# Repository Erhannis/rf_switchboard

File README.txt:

KiCAD pcb; whole bunch of RF-related modules, so I can figure out what works and how.  I'm a novice, don't trust my boards too hard.

Contains:
1x RP2040 with breakout headers
1x Micro-USB connector for 5V, 3V, and programming the RP2040
2x Tayloe Detectors (1x variable gain)
3x Ferrite feedthroughs (various ends)
2x 50Ω Loads
4x Shorts
Several inductors, assorted
Several capacitors, assorted
2x Headphone jacks
2x Amplifiers (1x variable gain)
1x 50MHz high pass filter
1x 800KHz high pass filter
1x 1MHz low pass filter
2x (1-10)MHz band pass filter (two arrangements)
5x LEDs, different colors
2x Laser diodes, different colors
2x Photodiode modules (2x with variable gain, 1x with 16Hz high pass)
2x Microphones
1x Speaker
3x RF mixers (various configurations)
2x De/mux (various configurations)
1x 2.5KHz-200MHz clock
1x DC boost converter (variable)
1x Constant current source (variable)
6x Attenuators (various strengths and topologies, 2x variable)
4x Buttons
8x Junctions
2x Header pin / U.FL adapter sets (4 each)
4x RF switches (two configurations)
2x NFET/PFET pairs
...and anything else I missed.

Everything MIT licensed, except a lot of the Tayloe module stuff I got from https://github.com/michalin/easysdr licensed GPL, though most of THAT came from the original Tayloe Detector paper https://www.norcalqrp.org/files/Tayloe_mixer_x3a.pdf, so I dunno how that works exactly.

-Erhannis

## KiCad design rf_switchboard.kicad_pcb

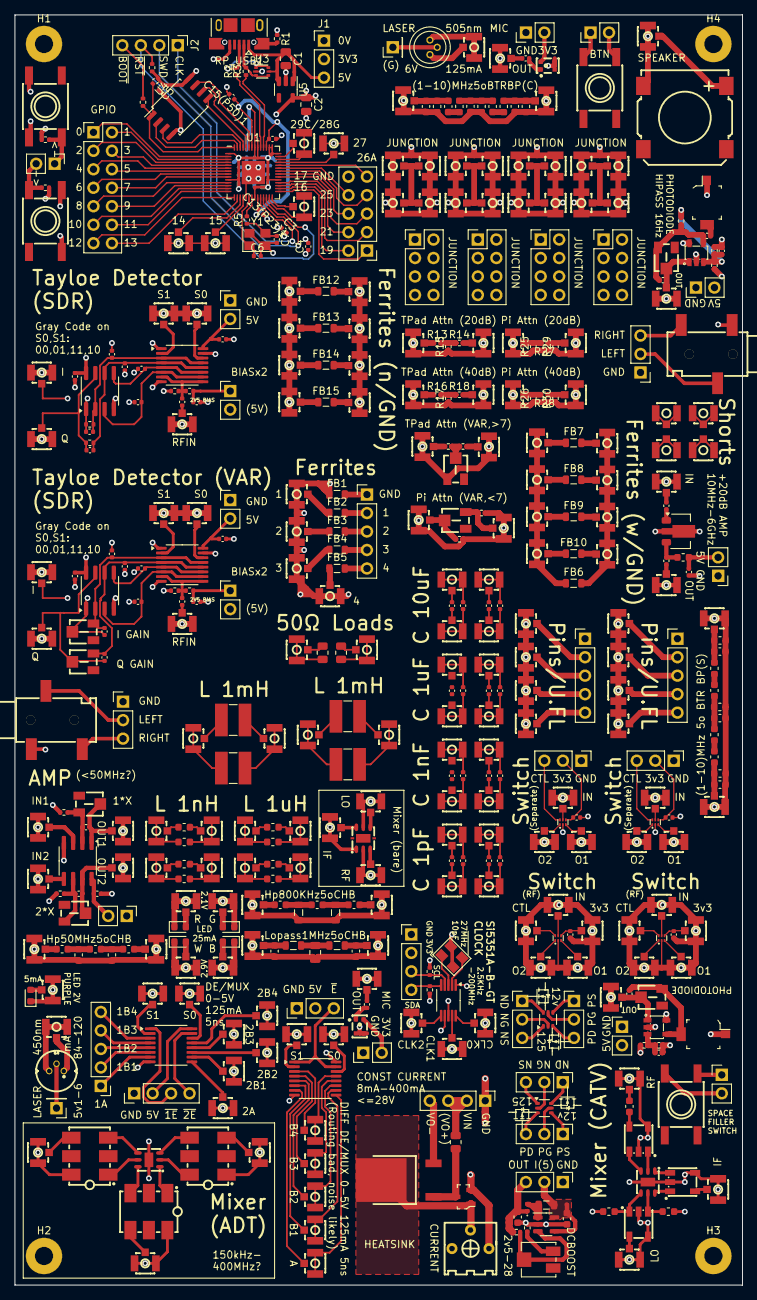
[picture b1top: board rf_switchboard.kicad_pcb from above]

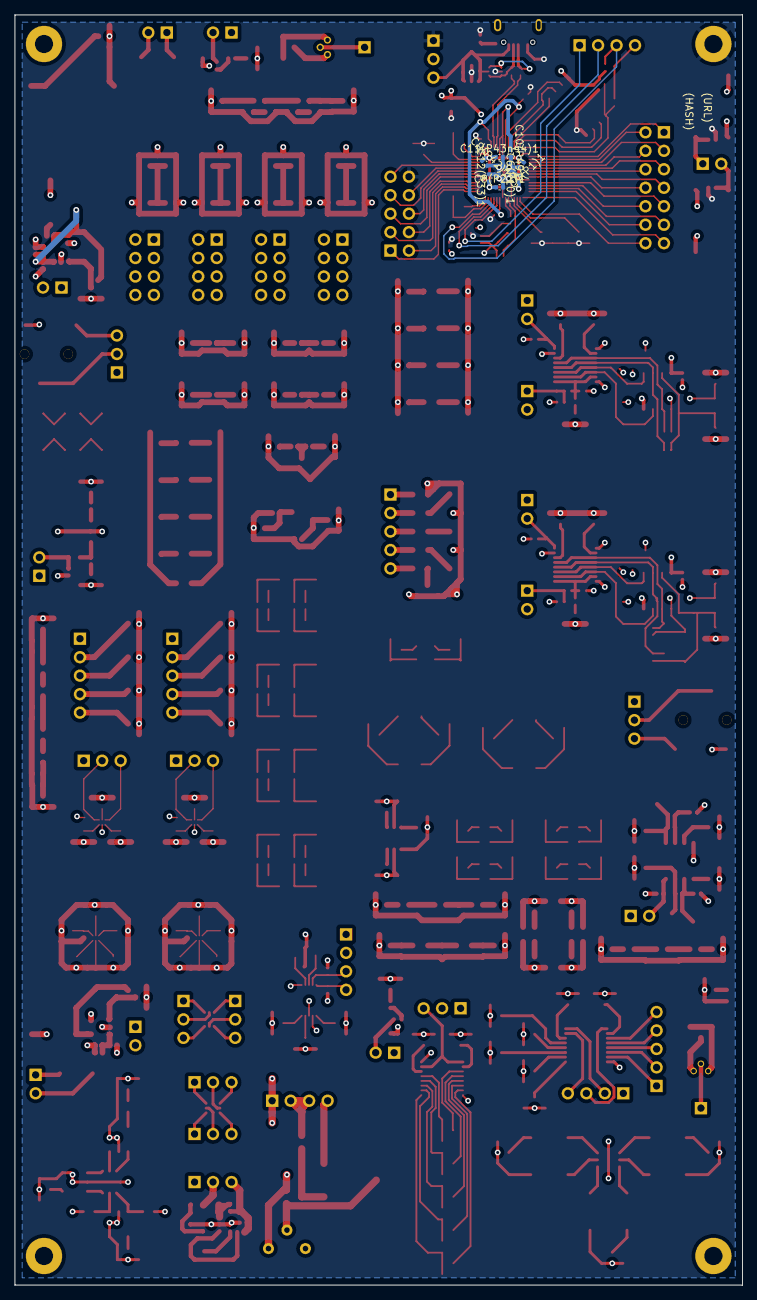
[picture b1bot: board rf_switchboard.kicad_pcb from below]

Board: 4 copper layers, 100.0 x 174.6 mm, 467 parts (7 on the bottom side), 421 nets.

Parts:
C1, C2: 10uF; C_0805_2012Metric
C1_1_10_5B1, C1_1_10_5B2, C5_1_10_5B1, C5_1_10_5B2: 218.6pF; C_0603_1608Metric
C1_HA1, C2_HA1, C3_HA1: C; C_0402_1005Metric
C1_HP1: 56pF; C_0603_1608Metric
C1_HP2, C1_LP1, C3_HP2, C3_LP1: 3.6nF; C_0603_1608Metric
C1_LA1, C2_LA1: 27pF; C_0402_1005Metric
C1_MIC1, C1_MIC2, C19, C20, C27, C28: 10uF; C_0402_1005Metric
C1_PR1, C1_PRH1: 3.3pF; C_0402_1005Metric
C1_TD1, C1_TDV1, C2_TD1, C2_TDV1, C3_TD1, C3_TDV1, C4_TD1, C4_TDV1: 220nF; C_0402_1005Metric
C1_VARB1, C2_VARB1: 10uF; C_0603_1608Metric
C2_1_10_5B1, C2_1_10_5B2, C4_1_10_5B1, C4_1_10_5B2: 1.771nF; C_0603_1608Metric
C2_HP1: 33pF; C_0603_1608Metric
C2_HP2: 2nF; C_0603_1608Metric
C2_LP1: 6.2nF; C_0805_2012Metric
C2_PR1, C2_PRH1, C3_LA1, C7_TD1, C7_TDV1, C8_TD1, C8_TDV1, C9_TD1, C9_TDV1, C11(P43n44)1, C12_TD1, C12_TDV1, C14(P45)1, C17, C18, C25, C26: 1uF; C_0402_1005Metric
C3, C4, C5, C6(P10)1, C7(P1)1, C8, C8(P22)1, C9, C9(P42)1, C10, C10(P49)1, C11, C12(P33)1, C13(P23)1, C15(P50)1: 100nF; C_0402_1005Metric
C3_1_10_5B1, C3_1_10_5B2: 707.4pF; C_0603_1608Metric
C3_HP1: 56nF; C_0603_1608Metric
C3_PRH1, C15, C16, C23, C24: 1nF; C_0402_1005Metric
C6, C7: 35pF; C_0402_1005Metric
C10_TD1, C10_TDV1, C11_TD1, C11_TDV1: 470pF; C_0402_1005Metric
C12: 3pF; C_0603_1608Metric
C13, C14, C21, C22: 1pF; C_0402_1005Metric
D1_LAS1: GH05035A2G; OPTO-TH_GH05035A2G
D1_LAS2: GH04580A2GX; LED-TH_3P-BD5.6-P1.00
D1_LEDS1: Red; LED_0603_1608Metric
D1_LEDS2: Purple; LED_0603_1608Metric
D1_VARB1: D_Schottky; D_0402_1005Metric
D2_LEDS1: Green; LED_0603_1608Metric
D3_LEDS1: Blue; LED_0603_1608Metric
D4_LEDS1: White; LED_0603_1608Metric
FB1, FB2, FB3, FB4, FB5, FB6, FB7, FB8, FB9, FB10, FB12, FB13, FB14, FB15: FerriteBead; L_0805_2012Metric
H1, H2, H3, H4: MountingHole_Pad; MountingHole_2.5mm_Pad
J1, J1_3S1, J1_3S2, J1_3S3, J1_3S4, J1_DM2, J1_VARB1: Conn_01x03_Pin; PinHeader_1x03_P2.54mm_Vertical
J1_CCV1, J1_DM1, J2, J18: Conn_01x04_Pin; PinHeader_1x04_P2.54mm_Vertical
J1_HP1, J1_HP2, J1_LAS1, J1_LAS2, J1_LEDS1, J1_LEDS2, J1_LP1, J2_DM1, J2_DM2, J2_HP1, J2_HP2, J2_LEDS1, J2_LP1, J2_MIC1, J2_MIC2, J3_DM1, J3_DM2, J3_LEDS1, J4_LEDS1, J5_DM1, J5_DM2, J6_DM1, J6_DM2, J7_DM1, J7_DM2, J8_DM1, J8_DM2, J9_DM1, J9_DM2: BWU.FL-IPEX1; IPEX-SMD_BWIPX-1-001E
J1_LA1, J1_MIC1, J1_MIC2, J1_PR1, J1_PRH1, J1_SS1, J1_SS2, J1_SS3, J10, J11, J15, J16, J19: Conn_01x02_Pin; PinHeader_1x02_P2.54mm_Vertical
J2_LAS1, J2_LAS2: Conn_01x01_Pin; PinHeader_1x01_P2.54mm_Vertical
J3, J4, J4_DM1, J5: Conn_01x05_Pin; PinHeader_1x05_P2.54mm_Vertical
J6, J7, J8, J9: Conn_02x04_Counter_Clockwise; PinHeader_2x04_P2.54mm_Vertical
J12, J13: PJ-320B; AUDIO-SMD_PJ-320B
J14: Conn_02x07_Odd_Even; PinHeader_2x07_P2.54mm_Vertical
J17: Conn_02x05_Odd_Even; PinHeader_2x05_P2.54mm_Vertical
JI1_LA1, JI2_LA1: BWU.FL-IPEX1; IPEX-SMD_BWIPX-1-001E
JN1_FET1, JN1_FET2: Conn_01x03_Pin; PinHeader_1x03_P2.54mm_Vertical
JO1_LA1, JO1_PR1, JO1_PRH1, JO2_LA1: BWU.FL-IPEX1; IPEX-SMD_BWIPX-1-001E
JP1_FET1, JP1_FET2: Conn_01x03_Pin; PinHeader_1x03_P2.54mm_Vertical
L1, L2: 4.7nH; L_0603_1608Metric
L1_1_10_5B1, L1_1_10_5B2, L5_1_10_5B1, L5_1_10_5B2: 11.59uH; L_0603_1608Metric
L1_HA1: 33uH; L_0603_1608Metric
L1_HP1, L2_HP1: 10uH; L_0603_1608Metric
L1_HP2, L2_HP2: 7.5uH; L_0805_2012Metric
L1_LP1, L2_LP1: 10uH; L_0805_2012Metric
L1_VARB1: L 10uH; L_0805_2012Metric
L2_1_10_5B1, L2_1_10_5B2, L4_1_10_5B1, L4_1_10_5B2: 1.431uH; L_0603_1608Metric
L3, L4, L5, L6: 1nH; L_0603_1608Metric
L3_1_10_5B1, L3_1_10_5B2: 3.581uH; L_0603_1608Metric
L7, L8, L11, L12: 1uH; L_0603_1608Metric
L9, L10, L13, L14: 1mH; L_Ferrocore_DLG-0403
POW1_VARB1: LM27313XMF; SOT-23-5
PV1_PR1, PV1_PRH1: BPW_34_S-Z; LED_2-SMD_Gull_Wing_4.4x3.85mm
Q1_CCV1: MOT13003D; TO-252-3_L6.5-W5.9-P4.60-LS10.0-BL
Q1_FET1, Q1_FET2: BSD235C; SOT-363_SC-70-6
Q2_CCV1: SS8050; SOT-23-3
R1: 1M; R_0402_1005Metric
R1_CCV1: 3.3k; R_0805_2012Metric
R1_LA1, R2_LA1, R6: 1k; R_0402_1005Metric
R1_PR1, R1_PRH1: 13.7k; R_0402_1005Metric
R1_SI5351AB1, R2_SI5351AB1, R4, R7: 10K; R_0402_1005Metric
R1_SS1, R2_SS1: 3.3k; R_0402_1005Metric
R1_TD1, R1_TDV1, R2_TD1, R2_TDV1, R3_TD1, R4_TD1: 10k; R_0402_1005Metric
R1_VARB1: R 100k 1%; R_0402_1005Metric
R2, R3: 27; R_0402_1005Metric
R2_PR1, R2_PRH1: 280; R_0402_1005Metric
R2_VARB1: R 4.53k 1%; R_0402_1005Metric
R3_PRH1: 10M; R_0402_1005Metric
R3_TDV1, R4_TDV1: 500k; RES-ADJ-SMD_3313J-1
R5: 1K; R_0402_1005Metric
R9, R10, R11, R12: FM8625H; DFN-6_L1.1-W0.7-P0.40-BL
R13, R14: 41.2; R_0402_1005Metric
R15: 10; R_0402_1005Metric
R16, R18: 48.7; R_0402_1005Metric
R17: 1; R_0402_1005Metric
R19, R21: 43; R_0402_1005Metric
R20, R23: 50; RES-ADJ-SMD_3313J-1
R22, R24: 200; R_0402_1005Metric
R25, R29: 62; R_0402_1005Metric
R26, R30: 51; R_0402_1005Metric
R27: 249; R_0402_1005Metric
R28: 2.49k; R_0402_1005Metric
R31, R32: 51Ω; R_0805_2012Metric
RP_USB1: USB_B_Micro; USB_Micro-B_XKB_U254-051T-4BH83-F1S
RV1_VARB1: 100k R_Potentiometer; Potentiometer_Bourns_3314J_Vertical
SPK1: GSPK1304S-8R0.5W; BUZ-SMD_4P-L13.0-W13.0-P11.4-BL
SW1_SS1, SW1_SS2, SW1_SS3, SW2_SS1: K2-1157SP-I4SW-04; SW-SMD_4P-L6.2-W6.2-P4.50-LS8.6
U1: RP2040; QFN-56-1EP_7x7mm_P0.4mm_EP3.2x3.2mm
U1_DM1, U1_DM2, U1_TD1, U1_TDV1: SN74CBT3253; TSSOP-16_4.4x5mm_P0.65mm
U1_HA1: GVA-63; SOT-89-3
U1_JU1, U1_JU2, U1_JU3, U1_JU4, U2, U2_JU1, U2_JU2, U2_JU3, U2_JU4, U3_JU1, U3_JU2, U3_JU3, U3_JU4, U4_JU1, U4_JU2, U4_JU3, U4_JU4, U6, U7, U8, U9, U10, U11, U12, U13, U14, U15, U16, U17, U18, U19, U20, U21, U22, U23, U24, U25, U26, U27, U28, U29, U30, U31, U32, U33, U34, U35, U36, U37, U38, U39, U40, U41, U42, U43, U44, U45, U47, U48, U49, U50, U51, U52, U53, U54, U55, U56, U57, U58, U59, U60, U61, U62, U63, U64, U65, U66, U67, U68, U69, U70, U72, U74, U77, U78, U79, U81, U82, U83, U84, U85, U86, U87, U88, U89, U90, U91, U92, U93, U94, U95, U96, U97, U98, U99, U100, U101, U102, U103, U104, U105, U106, U107, U108, U109, U110, U111, U112, U113, U114, U115, U116, U117, U118, U119, U120, U121, U122, U123, U124, U125, U126, U127, U128, U129, U130, U131, U132, U133, U134: BWU.FL-IPEX1; IPEX-SMD_BWIPX-1-001E
U1_LA1, U2_TD1, U2_TDV1: LM4562; SOIC-8_3.9x4.9mm_P1.27mm
U1_MIC1, U1_MIC2: ZTS6117H; MIC-SMD_4P-L2.8-W1.9-P1.84-TL_ZTS6117
U1_PR1, U1_PRH1: OPA320AIDBVR; SOT-23-5_L3.0-W1.7-P0.95-LS2.8-BR
U1_SI5351AB1: Si5351A-B-GT; MSOP-10_3x3mm_P0.5mm
U3: USBLC6-2P6; SOT-666
U4: W25Q128JVS; SOIC-8_5.23x5.23mm_P1.27mm
U5: AP2112K-3.3; SOT-23-5
U46, U73, U80: PE4140B-Z; DFN-6_L3.0-W3.0-P0.95-BL-EP-PE4140B-Z
U71, U75, U76: ETC1.6-4-2-3TR; FILTER-SMD_ETC4-1-2TR
VR1_CCV1: 3362P-1-101LF; RES-ADJ-TH_3362P-1-104LF
VR1_LA1, VR2_LA1: 500k; RES-ADJ-SMD_3313J-1
VR1_PR1, VR1_PRH1: 2M; RES-ADJ-SMD_3313J-1
X1, X2, X3: ADT1-1+; XFMR-SMD_6P-L7.9-W5.6-P2.54-LS7.0-BL
X1_SI5351AB1: 27MHz; OSC-SMD_4P-L3.2-W2.5-BL
Y1: 12MHz; Crystal_SMD_3225-4Pin_3.2x2.5mm

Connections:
+1V2: C13(P23)1.1, C14(P45)1.1, C15(P50)1.1, U1.23 (DVDD), U1.45 (VREG_VOUT), U1.50 (DVDD)
+3V3: C2.1, C3.1, C4.1, C5.1, C6(P10)1.1, C7(P1)1.1, C8(P22)1.1, C9(P42)1.1, C10(P49)1.1, C11(P43n44)1.1, C12(P33)1.1, J1.2, R4.1, R7.2, SW1_SS1.3, SW1_SS1.4, SW2_SS1.3, SW2_SS1.4, U1.1 (IOVDD), U1.10 (IOVDD), U1.22 (IOVDD), U1.33 (IOVDD), U1.42 (IOVDD), U1.43 (ADC_AVDD), U1.44 (VREG_IN), U1.48 (USB_VDD), U1.49 (IOVDD), U4.8 (VCC), U5.5 (VOUT)
+5V: C1.1, J1.3, RP_USB1.1 (VBUS), U3.5 (VBUS), U5.1 (VIN), U5.3 (EN)
/1_10_5x_butter1/IN+: C1_1_10_5B2.1, C2_1_10_5B2.1, L1_1_10_5B2.1, U9.1
/1_10_5x_butter1/IN-: C1_1_10_5B2.2, C3_1_10_5B2.2, C5_1_10_5B2.2, L1_1_10_5B2.2, L3_1_10_5B2.2, L5_1_10_5B2.2, U9.2, U9.3, U10.2, U10.3
/1_10_5x_butter1/OUT+: C5_1_10_5B2.1, L4_1_10_5B2.2, L5_1_10_5B2.1, U10.1
/1_10_5x_butter/IN+: C1_1_10_5B1.1, C2_1_10_5B1.1, L1_1_10_5B1.1, U7.1
/1_10_5x_butter/IN-: C1_1_10_5B1.2, C3_1_10_5B1.2, C5_1_10_5B1.2, L1_1_10_5B1.2, L3_1_10_5B1.2, L5_1_10_5B1.2, U7.2, U7.3, U8.2, U8.3
/1_10_5x_butter/OUT+: C5_1_10_5B1.1, L4_1_10_5B1.2, L5_1_10_5B1.1, U8.1
/QSPI_CS: R6.1, R7.1, U1.56 (QSPI_SS), U4.1 (~CS)
/QSPI_DATA[0]: U1.53 (QSPI_SD0), U4.5 (DI(IO0))
/QSPI_DATA[1]: U1.55 (QSPI_SD1), U4.2 (DO(IO1))
/QSPI_DATA[2]: U1.54 (QSPI_SD2), U4.3 (IO2)
/QSPI_DATA[3]: U1.51 (QSPI_SD3), U4.7 (IO3)
/QSPI_SCK: U1.52 (QSPI_SCLK), U4.6 (CLK)
/RP_SWCLK: J2.1, U1.24 (SWCLK)
/RP_SWD: J2.2, U1.25 (SWD)
/RP_UD+: R2.1, U1.47 (USB_DP)
/RP_UD-: R3.1, U1.46 (USB_DM)
/USB_BOOT: J2.4, R6.2
/const_current_var1/GND: J1_CCV1.1, Q2_CCV1.2 (E), VR1_CCV1.3
/const_current_var1/VIN: J1_CCV1.2, J1_CCV1.3, R1_CCV1.1
/const_current_var1/VO-: J1_CCV1.4, Q1_CCV1.3 (C)
/dc_boost_var1/GND: C1_VARB1.1, C2_VARB1.1, J1_VARB1.1, POW1_VARB1.2 (GND), R2_VARB1.2
/dc_boost_var1/VIN: C1_VARB1.2, J1_VARB1.2, L1_VARB1.1, POW1_VARB1.4 (EN), POW1_VARB1.5 (VIN)
/dc_boost_var1/VOUT: C2_VARB1.2, D1_VARB1.1 (K), J1_VARB1.3, R1_VARB1.1
/hi_amp1/5V: C2_HA1.1, J19.2, L1_HA1.1
/hi_amp1/GND: C2_HA1.2, J19.1, U1_HA1.2 (GND), U133.2, U133.3, U134.2, U134.3
/hi_amp1/RFIN: C1_HA1.1, U133.1
/hi_amp1/RFOUT: C3_HA1.2, U134.1
/lo_amp1/5V: C3_LA1.1, J1_LA1.2, U1_LA1.8 (V+)
/lo_amp1/GND: C3_LA1.2, J1_LA1.1, JI1_LA1.2, JI1_LA1.3, JI2_LA1.2, JI2_LA1.3, JO1_LA1.2, JO1_LA1.3, JO2_LA1.2, JO2_LA1.3, R1_LA1.2, R2_LA1.2, U1_LA1.4 (V-)
/lo_amp1/IN1: JI1_LA1.1, U1_LA1.3 (+)
/lo_amp1/IN2: JI2_LA1.1, U1_LA1.5 (+)
/lo_amp1/OUT1: C1_LA1.2, JO1_LA1.1, U1_LA1.1, VR1_LA1.2
/lo_amp1/OUT2: C2_LA1.2, JO2_LA1.1, U1_LA1.7, VR2_LA1.2
/mixer_catv/GND: L1.2, L2.2, U70.2, U70.3, U71.2 (S), U71.5, U72.2, U72.3, U73.7 (PAD), U74.2, U74.3, U75.2 (S), U75.4, U76.2 (S), U76.4
/photo_rx1/5V: J1_PR1.2, R1_PR1.1, U1_PR1.5 (V+)
/photo_rx1/GND: C2_PR1.2, J1_PR1.1, JO1_PR1.2, JO1_PR1.3, PV1_PR1.A, R2_PR1.2, U1_PR1.2 (V-)
/photo_rx1/OUT: C1_PR1.2, JO1_PR1.1, U1_PR1.1 (OUT), VR1_PR1.2
/photo_rx_highpass1/5V: J1_PRH1.2, R1_PRH1.1, U1_PRH1.5 (V+)
/photo_rx_highpass1/GND: C2_PRH1.2, J1_PRH1.1, JO1_PRH1.2, JO1_PRH1.3, PV1_PRH1.A, R2_PRH1.2, U1_PRH1.2 (V-)
/photo_rx_highpass1/OUT: C1_PRH1.2, JO1_PRH1.1, U1_PRH1.1 (OUT), VR1_PRH1.2
/si5351ab1/3V3: J18.2, R1_SI5351AB1.1, R2_SI5351AB1.1, U1_SI5351AB1.1 (VDD), U1_SI5351AB1.7 (VDDO)
/si5351ab1/CLK0: U1_SI5351AB1.10 (CLK0), U130.1
/si5351ab1/CLK1: U1_SI5351AB1.9 (CLK1), U131.1
/si5351ab1/CLK2: U1_SI5351AB1.6 (CLK2), U132.1
/si5351ab1/GND: J18.1, U1_SI5351AB1.8 (GND), U130.2, U130.3, U131.2, U131.3, U132.2, U132.3, X1_SI5351AB1.2 (GND), X1_SI5351AB1.4 (GND)
/si5351ab1/SCL: J18.3, R1_SI5351AB1.2, U1_SI5351AB1.4 (SCL)
/si5351ab1/SDA: J18.4, R2_SI5351AB1.2, U1_SI5351AB1.5 (SDA)
/tayloe_detector/5V: C8_TD1.2, C12_TD1.1, J10.2, J15.2, U1_TD1.16 (VCC), U2_TD1.8 (V+)
/tayloe_detector/BIASx2: C9_TD1.1, J15.1, R1_TD1.1
/tayloe_detector/GND: C1_TD1.2, C2_TD1.2, C3_TD1.2, C4_TD1.2, C8_TD1.1, C9_TD1.2, C12_TD1.2, J10.1, R2_TD1.2, U1_TD1.1 (1~OE), U1_TD1.8 (GND), U1_TD1.15 (2~OE), U2_TD1.4 (V-), U78.2, U78.3, U79.2, U79.3, U82.2, U82.3, U84.2, U84.3, U85.2, U85.3
/tayloe_detector/I: C10_TD1.2, R3_TD1.2, U2_TD1.1, U84.1
/tayloe_detector/Q: C11_TD1.2, R4_TD1.2, U2_TD1.7, U85.1
/tayloe_detector/RFIN: C7_TD1.1, U78.1
/tayloe_detector/S0: U1_TD1.14 (S0), U79.1
/tayloe_detector/S1: U1_TD1.2 (S1), U82.1
/tayloe_detector_var/5V: C8_TDV1.2, C12_TDV1.1, J11.2, J16.2, U1_TDV1.16 (VCC), U2_TDV1.8 (V+)
/tayloe_detector_var/BIASx2: C9_TDV1.1, J16.1, R1_TDV1.1
/tayloe_detector_var/GND: C1_TDV1.2, C2_TDV1.2, C3_TDV1.2, C4_TDV1.2, C8_TDV1.1, C9_TDV1.2, C12_TDV1.2, J11.1, R2_TDV1.2, U1_TDV1.1 (1~OE), U1_TDV1.8 (GND), U1_TDV1.15 (2~OE), U2_TDV1.4 (V-), U86.2, U86.3, U87.2, U87.3, U88.2, U88.3, U89.2, U89.3, U90.2, U90.3
/tayloe_detector_var/I: C10_TDV1.2, R3_TDV1.2, U2_TDV1.1, U89.1
/tayloe_detector_var/Q: C11_TDV1.2, R4_TDV1.2, U2_TDV1.7, U90.1
/tayloe_detector_var/RFIN: C7_TDV1.1, U88.1
/tayloe_detector_var/S0: U1_TDV1.14 (S0), U86.1
/tayloe_detector_var/S1: U1_TDV1.2 (S1), U87.1
/~RESET: J2.3, R4.2, U1.26 (RUN)
GND: C1.2, C2.2, C3.2, C4.2, C5.2, C6.2, C6(P10)1.2, C7.2, C7(P1)1.2, C8(P22)1.2, C9(P42)1.2, C10(P49)1.2, C11(P43n44)1.2, C12(P33)1.2, C13(P23)1.2, C14(P45)1.2, C15(P50)1.2, H1.1, J1.1, J17.10, R1.1, R1_SS1.1, R2_SS1.2, RP_USB1.5 (GND), U1.19 (TESTEN), U1.57 (GND), U3.2 (GND), U4.4 (GND), U5.2 (GND), U126.2, U126.3, U128.2, U128.3, U129.2, U129.3, Y1.2, Y1.4
GND_DM1: J1_DM1.1, J2_DM1.2, J2_DM1.3, J3_DM1.2, J3_DM1.3, J5_DM1.2, J5_DM1.3, J6_DM1.2, J6_DM1.3, J7_DM1.2, J7_DM1.3, J8_DM1.2, J8_DM1.3, J9_DM1.2, J9_DM1.3, U1_DM1.8 (GND)
GND_DM2: J1_DM2.1, J2_DM2.2, J2_DM2.3, J3_DM2.2, J3_DM2.3, U1_DM2.8 (GND)
unnamed: C1_HA1.2, U1_HA1.1
unnamed: C1_HP1.1, J1_HP1.1
unnamed: C1_HP1.2, C2_HP1.1, L1_HP1.2
unnamed: C1_HP2.1, J1_HP2.1
unnamed: C1_HP2.2, C2_HP2.1, L1_HP2.2
unnamed: C1_LP1.1, J1_LP1.1, L1_LP1.1
unnamed: C1_LP1.2, C2_LP1.2, C3_LP1.2, J1_LP1.2, J1_LP1.3, J2_LP1.2, J2_LP1.3
unnamed: C1_MIC1.1, J2_MIC1.1
unnamed: C1_MIC2.1, J2_MIC2.1
unnamed: C2_1_10_5B1.2, L2_1_10_5B1.1
unnamed: C2_1_10_5B2.2, L2_1_10_5B2.1
unnamed: C2_HP1.2, C3_HP1.1, L2_HP1.2
unnamed: C2_HP2.2, C3_HP2.1, L2_HP2.2
unnamed: C2_LP1.1, L1_LP1.2, L2_LP1.1
unnamed: C3_1_10_5B1.1, C4_1_10_5B1.1, L2_1_10_5B1.2, L3_1_10_5B1.1
unnamed: C3_1_10_5B2.1, C4_1_10_5B2.1, L2_1_10_5B2.2, L3_1_10_5B2.1
unnamed: C3_HA1.1, L1_HA1.2, U1_HA1.3
unnamed: C3_HP1.2, J2_HP1.1
unnamed: C3_HP2.2, J2_HP2.1
unnamed: C3_LP1.1, J2_LP1.1, L2_LP1.2
unnamed: C3_PRH1.1, PV1_PRH1.K
unnamed: C4_1_10_5B1.2, L4_1_10_5B1.1
unnamed: C4_1_10_5B2.2, L4_1_10_5B2.1
unnamed: C7.1, R5.1, Y1.3
unnamed: C12.1, U70.1
unnamed: C12.2, U71.4
unnamed: C13.1, U103.1
unnamed: C13.2, U104.1
unnamed: C14.1, U103.2, U103.3
unnamed: C14.2, U104.2, U104.3
unnamed: C15.1, U105.1
unnamed: C15.2, U106.1
unnamed: C16.1, U105.2, U105.3
unnamed: C16.2, U106.2, U106.3
unnamed: C17.1, U107.1
unnamed: C17.2, U108.1
unnamed: C18.1, U107.2, U107.3
unnamed: C18.2, U108.2, U108.3
unnamed: C19.1, U109.1
unnamed: C19.2, U110.1
unnamed: C20.1, U109.2, U109.3
unnamed: C20.2, U110.2, U110.3
unnamed: C21.1, U111.1
unnamed: C21.2, U115.1
unnamed: C22.1, U111.2, U111.3
unnamed: C22.2, U115.2, U115.3
unnamed: C23.1, U112.1
unnamed: C23.2, U116.1
unnamed: C24.1, U112.2, U112.3
unnamed: C24.2, U116.2, U116.3
unnamed: C25.1, U113.1
unnamed: C25.2, U117.1
unnamed: C26.1, U113.2, U113.3
unnamed: C26.2, U117.2, U117.3
unnamed: C27.1, U114.1
unnamed: C27.2, U118.1
unnamed: C28.1, U114.2, U114.3
unnamed: C28.2, U118.2, U118.3
unnamed: D1_LAS1.1 (A), J1_LAS1.1
unnamed: D1_LAS1.3 (K), J1_LAS1.2, J1_LAS1.3
unnamed: D1_LAS2.1 (A), J1_LAS2.1
unnamed: D1_LAS2.3 (K), J1_LAS2.2, J1_LAS2.3
unnamed: D1_LEDS1.2 (A), J1_LEDS1.1
unnamed: D1_LEDS1.1 (K), J1_LEDS1.2, J1_LEDS1.3
unnamed: D1_LEDS2.2 (A), J1_LEDS2.1
unnamed: D1_LEDS2.1 (K), J1_LEDS2.2, J1_LEDS2.3
unnamed: D1_VARB1.2 (A), L1_VARB1.2, POW1_VARB1.1 (SW)
unnamed: D2_LEDS1.2 (A), J2_LEDS1.1
unnamed: D2_LEDS1.1 (K), J2_LEDS1.2, J2_LEDS1.3
unnamed: D3_LEDS1.2 (A), J3_LEDS1.1
unnamed: D3_LEDS1.1 (K), J3_LEDS1.2, J3_LEDS1.3
unnamed: D4_LEDS1.2 (A), J4_LEDS1.1
unnamed: D4_LEDS1.1 (K), J4_LEDS1.2, J4_LEDS1.3
unnamed: FB1.1, U26.2, U26.3, U27.2, U27.3, U28.2, U28.3, U29.2, U29.3
unnamed: FB2.1, U26.1
unnamed: FB3.1, U27.1
unnamed: FB4.1, U28.1
unnamed: FB5.1, U29.1
unnamed: FB6.1, U30.2, U30.3, U31.2, U31.3, U32.2, U32.3, U33.2, U33.3
unnamed: FB6.2, U34.2, U34.3, U35.2, U35.3, U36.2, U36.3, U37.2, U37.3
unnamed: FB7.1, U30.1
unnamed: FB7.2, U34.1
unnamed: FB8.1, U31.1
unnamed: FB8.2, U35.1
unnamed: FB9.1, U32.1
unnamed: FB9.2, U36.1
unnamed: FB10.1, U33.1
unnamed: FB10.2, U37.1
unnamed: FB12.1, U59.1
unnamed: FB12.2, U60.1
unnamed: FB13.1, U61.1
unnamed: FB13.2, U62.1
unnamed: FB14.1, U63.1
unnamed: FB14.2, U64.1
unnamed: FB15.1, U65.1
unnamed: FB15.2, U66.1
unnamed: C8.1, J1_3S1.1, R9.2 (GND)
unnamed: C8.2, J1_3S1.2, R9.4 (VDD)
unnamed: J1_3S1.3, R9.6 (VCTL)
unnamed: C10.1, J1_3S2.1, R12.2 (GND)
unnamed: C10.2, J1_3S2.2, R12.4 (VDD)
unnamed: J1_3S2.3, R12.6 (VCTL)
unnamed: J1_3S3.1, J12.1
unnamed: J1_3S3.2, J12.2
unnamed: J1_3S3.3, J12.3
unnamed: J1_3S4.1, J13.1
unnamed: J1_3S4.2, J13.2
unnamed: J1_3S4.3, J13.3
unnamed: J1_DM1.2, U1_DM1.16 (VCC)
unnamed: J1_DM1.3, U1_DM1.1 (1~OE)
unnamed: J1_DM1.4, U1_DM1.15 (2~OE)
unnamed: J1_DM2.2, U1_DM2.16 (VCC)
unnamed: J1_DM2.3, U1_DM2.1 (1~OE), U1_DM2.15 (2~OE)
unnamed: J1_HP1.2, J1_HP1.3, J2_HP1.2, J2_HP1.3, L1_HP1.1, L2_HP1.1
unnamed: J1_HP2.2, J1_HP2.3, J2_HP2.2, J2_HP2.3, L1_HP2.1, L2_HP2.1
unnamed: J1_MIC1.1, J2_MIC1.2, J2_MIC1.3, U1_MIC1.2 (GND), U1_MIC1.3 (GND)
unnamed: J1_MIC1.2, U1_MIC1.4 (VDD)
unnamed: J1_MIC2.1, J2_MIC2.2, J2_MIC2.3, U1_MIC2.2 (GND), U1_MIC2.3 (GND)
unnamed: J1_MIC2.2, U1_MIC2.4 (VDD)
unnamed: J1_SS1.1, R1_SS1.2, SW1_SS1.2
unnamed: J1_SS1.2, R2_SS1.1, SW2_SS1.2
unnamed: J1_SS2.1, SW1_SS2.2
unnamed: J1_SS2.2, SW1_SS2.4
unnamed: J1_SS3.1, SW1_SS3.4
unnamed: J1_SS3.2, SW1_SS3.2
unnamed: D1_LAS1.2 (K), J2_LAS1.1
unnamed: D1_LAS2.2, J2_LAS2.1
unnamed: J3.1, U38.2, U38.3, U39.2, U39.3, U40.2, U40.3, U41.2, U41.3
unnamed: J3.2, U38.1
unnamed: J3.3, U39.1
unnamed: J3.4, U40.1
unnamed: J3.5, U41.1
unnamed: FB1.2, J4.1
unnamed: FB2.2, J4.2
unnamed: FB3.2, J4.3
unnamed: FB4.2, J4.4
unnamed: FB5.2, J4.5
unnamed: J4_DM1.1, U1_DM1.7 (1A)
unnamed: J4_DM1.2, U1_DM1.6 (1B1)
unnamed: J4_DM1.3, U1_DM1.5 (1B2)
unnamed: J4_DM1.4, U1_DM1.4 (1B3)
unnamed: J4_DM1.5, U1_DM1.3 (1B4)
unnamed: J5.1, U42.2, U42.3, U43.2, U43.3, U44.2, U44.3, U45.2, U45.3
unnamed: J5.2, U42.1
unnamed: J5.3, U43.1
unnamed: J5.4, U44.1
unnamed: J5.5, U45.1
unnamed: J6.1, J6.2, J6.3, J6.4, J6.5, J6.6, J6.7, J6.8
unnamed: J7.1, J7.2, J7.3, J7.4, J7.5, J7.6, J7.7, J7.8
unnamed: J8.1, J8.2, J8.3, J8.4, J8.5, J8.6, J8.7, J8.8
unnamed: J9.1, J9.2, J9.3, J9.4, J9.5, J9.6, J9.7, J9.8
unnamed: J14.1, U1.2 (GPIO0)
unnamed: J14.2, U1.3 (GPIO1)
unnamed: J14.3, U1.4 (GPIO2)
unnamed: J14.4, U1.5 (GPIO3)
unnamed: J14.5, U1.6 (GPIO4)
unnamed: J14.6, U1.7 (GPIO5)
unnamed: J14.7, U1.8 (GPIO6)
unnamed: J14.8, U1.9 (GPIO7)
unnamed: J14.9, U1.11 (GPIO8)
unnamed: J14.10, U1.12 (GPIO9)
unnamed: J14.11, U1.13 (GPIO10)
unnamed: J14.12, U1.14 (GPIO11)
unnamed: J14.13, U1.15 (GPIO12)
unnamed: J14.14, U1.16 (GPIO13)
unnamed: J17.1, U1.29 (GPIO18)
unnamed: J17.2, U1.30 (GPIO19)
unnamed: J17.3, U1.31 (GPIO20)
unnamed: J17.4, U1.32 (GPIO21)
unnamed: J17.5, U1.34 (GPIO22)
unnamed: J17.6, U1.35 (GPIO23)
unnamed: J17.7, U1.36 (GPIO24)
unnamed: J17.8, U1.37 (GPIO25)
unnamed: J17.9, U1.38 (GPIO26_ADC0)
unnamed: JN1_FET1.1, Q1_FET1.6 (DN)
unnamed: JN1_FET1.2, Q1_FET1.2 (GN)
unnamed: JN1_FET1.3, Q1_FET1.1 (SN)
unnamed: JN1_FET2.1, Q1_FET2.6 (DN)
unnamed: JN1_FET2.2, Q1_FET2.2 (GN)
unnamed: JN1_FET2.3, Q1_FET2.1 (SN)
unnamed: JP1_FET1.1, Q1_FET1.4 (SP)
unnamed: JP1_FET1.2, Q1_FET1.5 (GP)
unnamed: JP1_FET1.3, Q1_FET1.3 (DP)
unnamed: JP1_FET2.1, Q1_FET2.4 (SP)
unnamed: JP1_FET2.2, Q1_FET2.5 (GP)
unnamed: JP1_FET2.3, Q1_FET2.3 (DP)
unnamed: L3.1, U91.1
unnamed: L3.2, U92.1
unnamed: L4.1, U91.2, U91.3
unnamed: L4.2, U92.2, U92.3
unnamed: L5.1, U93.1
unnamed: L5.2, U94.1
unnamed: L6.1, U93.2, U93.3
unnamed: L6.2, U94.2, U94.3
unnamed: L7.1, U95.1
unnamed: L7.2, U96.1
unnamed: L8.1, U95.2, U95.3
unnamed: L8.2, U96.2, U96.3
unnamed: L9.1, U97.1
unnamed: L9.2, U98.1
unnamed: L10.1, U97.2, U97.3
unnamed: L10.2, U98.2, U98.3
unnamed: L11.1, U99.1
unnamed: L11.2, U100.1
unnamed: L12.1, U99.2, U99.3
unnamed: L12.2, U100.2, U100.3
unnamed: L13.1, U101.1
unnamed: L13.2, U102.1
unnamed: L14.1, U101.2, U101.3
unnamed: L14.2, U102.2, U102.3
unnamed: POW1_VARB1.3 (FB), R1_VARB1.2, RV1_VARB1.2
unnamed: Q1_CCV1.1 (B), Q2_CCV1.3 (C), R1_CCV1.2
unnamed: Q1_CCV1.2 (E), Q2_CCV1.1 (B), VR1_CCV1.2
unnamed: R2_VARB1.1, RV1_VARB1.3
unnamed: R9.5 (AND), U12.1
unnamed: R9.3 (RF1), U2.1
unnamed: R9.1 (RF2), U11.1
unnamed: R10.5 (AND), U15.1
unnamed: C9.1, R10.2 (GND), U13.2, U13.3, U14.2, U14.3, U15.2, U15.3, U16.2, U16.3, U17.2, U17.3
unnamed: R10.3 (RF1), U14.1
unnamed: R10.1 (RF2), U13.1
unnamed: R10.6 (VCTL), U17.1
unnamed: C9.2, R10.4 (VDD), U16.1
unnamed: R11.5 (AND), U24.1
unnamed: C11.1, R11.2 (GND), U18.2, U18.3, U19.2, U19.3, U22.2, U22.3, U23.2, U23.3, U24.2, U24.3
unnamed: R11.3 (RF1), U19.1
unnamed: R11.1 (RF2), U18.1
unnamed: R11.6 (VCTL), U23.1
unnamed: C11.2, R11.4 (VDD), U22.1
unnamed: R12.5 (AND), U25.1
unnamed: R12.3 (RF1), U21.1
unnamed: R12.1 (RF2), U20.1
unnamed: R13.1, U47.1
unnamed: R13.2, R14.1, R15.2
unnamed: R14.2, U48.1
unnamed: R15.1, U47.2, U47.3, U48.2, U48.3
unnamed: R16.1, U49.1
unnamed: R16.2, R17.2, R18.1
unnamed: R17.1, U49.2, U49.3, U50.2, U50.3
unnamed: R18.2, U50.1
unnamed: R19.1, U51.1
unnamed: R19.2, R20.2, R21.1
unnamed: R20.3, U51.2, U51.3, U52.2, U52.3
unnamed: R21.2, U52.1
unnamed: R22.1, R24.1, U53.2, U53.3, U54.2, U54.3
unnamed: R22.2, R23.2, U53.1
unnamed: R23.1, R24.2, U54.1
unnamed: R25.1, R29.1, U55.2, U55.3, U57.2, U57.3
unnamed: R25.2, R27.2, U55.1
unnamed: R26.1, R30.1, U56.2, U56.3, U58.2, U58.3
unnamed: R26.2, R28.2, U56.1
unnamed: R27.1, R29.2, U57.1
unnamed: R28.1, R30.2, U58.1
unnamed: R31.1, U123.1
unnamed: R31.2, U123.2, U123.3
unnamed: R32.1, U124.1
unnamed: R32.2, U124.2, U124.3
unnamed: R2.2, RP_USB1.3 (D+), U3.1 (I/O1), U3.6 (I/O1)
unnamed: R3.2, RP_USB1.2 (D-), U3.3 (I/O2), U3.4 (I/O2)
unnamed: R1.2, RP_USB1.6 (Shield)
unnamed: SPK1.1 (+), U6.1
unnamed: SPK1.2, U6.2, U6.3
unnamed: U1.17 (GPIO14), U128.1
unnamed: U1.18 (GPIO15), U129.1
unnamed: U1.27 (GPIO16), U125.2, U125.3
unnamed: U1.28 (GPIO17), U125.1
unnamed: U1.39 (GPIO27_ADC1), U126.1
unnamed: U1.40 (GPIO28_ADC2), U127.2, U127.3
unnamed: U1.41 (GPIO29_ADC3), U127.1
unnamed: C6.1, U1.20 (XIN), Y1.1
unnamed: R5.2, U1.21 (XOUT)
unnamed: J5_DM1.1, U1_DM1.9 (2A)
unnamed: J6_DM1.1, U1_DM1.10 (2B1)
unnamed: J7_DM1.1, U1_DM1.11 (2B2)
unnamed: J8_DM1.1, U1_DM1.12 (2B3)
unnamed: J9_DM1.1, U1_DM1.13 (2B4)
unnamed: J2_DM1.1, U1_DM1.14 (S0)
unnamed: J3_DM1.1, U1_DM1.2 (S1)
unnamed: J5_DM2.1, U1_DM2.7 (1A)
unnamed: J6_DM2.1, U1_DM2.6 (1B1)
unnamed: J7_DM2.1, U1_DM2.5 (1B2)
unnamed: J8_DM2.1, U1_DM2.4 (1B3)
unnamed: J9_DM2.1, U1_DM2.3 (1B4)
unnamed: J5_DM2.2, J5_DM2.3, U1_DM2.9 (2A)
unnamed: J6_DM2.2, J6_DM2.3, U1_DM2.10 (2B1)
unnamed: J7_DM2.2, J7_DM2.3, U1_DM2.11 (2B2)
unnamed: J8_DM2.2, J8_DM2.3, U1_DM2.12 (2B3)
unnamed: J9_DM2.2, J9_DM2.3, U1_DM2.13 (2B4)
unnamed: J2_DM2.1, U1_DM2.14 (S0)
unnamed: J3_DM2.1, U1_DM2.2 (S1)
unnamed: U1_JU1.1, U2_JU1.1, U3_JU1.1, U4_JU1.1
unnamed: U1_JU1.2, U1_JU1.3, U2_JU1.2, U2_JU1.3, U3_JU1.2, U3_JU1.3, U4_JU1.2, U4_JU1.3
unnamed: U1_JU2.1, U2_JU2.1, U3_JU2.1, U4_JU2.1
unnamed: U1_JU2.2, U1_JU2.3, U2_JU2.2, U2_JU2.3, U3_JU2.2, U3_JU2.3, U4_JU2.2, U4_JU2.3
unnamed: U1_JU3.1, U2_JU3.1, U3_JU3.1, U4_JU3.1
unnamed: U1_JU3.2, U1_JU3.3, U2_JU3.2, U2_JU3.3, U3_JU3.2, U3_JU3.3, U4_JU3.2, U4_JU3.3
unnamed: U1_JU4.1, U2_JU4.1, U3_JU4.1, U4_JU4.1
unnamed: U1_JU4.2, U1_JU4.3, U2_JU4.2, U2_JU4.3, U3_JU4.2, U3_JU4.3, U4_JU4.2, U4_JU4.3
unnamed: C1_LA1.1, R1_LA1.1, U1_LA1.2 (-), VR1_LA1.1
unnamed: C2_LA1.1, R2_LA1.1, U1_LA1.6 (-), VR2_LA1.1
unnamed: C1_MIC1.2, U1_MIC1.1 (OUT)
unnamed: C1_MIC2.2, U1_MIC2.1 (OUT)
unnamed: C2_PR1.1, R1_PR1.2, R2_PR1.1, U1_PR1.3 (IN+)
unnamed: C1_PR1.1, PV1_PR1.K, U1_PR1.4 (IN-), VR1_PR1.1
unnamed: C2_PRH1.1, R1_PRH1.2, R2_PRH1.1, R3_PRH1.2, U1_PRH1.3 (IN+)
unnamed: C1_PRH1.1, C3_PRH1.2, R3_PRH1.1, U1_PRH1.4 (IN-), VR1_PRH1.1
unnamed: U1_SI5351AB1.2 (XA), X1_SI5351AB1.3 (OSC2)
unnamed: U1_SI5351AB1.3 (XB), X1_SI5351AB1.1 (OSC1)
unnamed: C7_TD1.2, R1_TD1.2, R2_TD1.1, U1_TD1.7 (1A), U1_TD1.9 (2A)
unnamed: C1_TD1.1, U1_TD1.6 (1B1), U1_TD1.10 (2B1), U2_TD1.3 (+)
unnamed: C3_TD1.1, U1_TD1.5 (1B2), U1_TD1.11 (2B2), U2_TD1.5 (+)
unnamed: C4_TD1.1, C11_TD1.1, R4_TD1.1, U1_TD1.4 (1B3), U1_TD1.12 (2B3), U2_TD1.6 (-)
unnamed: C2_TD1.1, C10_TD1.1, R3_TD1.1, U1_TD1.3 (1B4), U1_TD1.13 (2B4), U2_TD1.2 (-)
unnamed: C7_TDV1.2, R1_TDV1.2, R2_TDV1.1, U1_TDV1.7 (1A), U1_TDV1.9 (2A)
unnamed: C1_TDV1.1, U1_TDV1.6 (1B1), U1_TDV1.10 (2B1), U2_TDV1.3 (+)
unnamed: C3_TDV1.1, U1_TDV1.5 (1B2), U1_TDV1.11 (2B2), U2_TDV1.5 (+)
unnamed: C4_TDV1.1, C11_TDV1.1, R4_TDV1.1, U1_TDV1.4 (1B3), U1_TDV1.12 (2B3), U2_TDV1.6 (-)
unnamed: C2_TDV1.1, C10_TDV1.1, R3_TDV1.1, U1_TDV1.3 (1B4), U1_TDV1.13 (2B4), U2_TDV1.2 (-)
unnamed: U2.2, U2.3, U11.2, U11.3, U12.2, U12.3
unnamed: U20.2, U20.3, U21.2, U21.3, U25.2, U25.3
unnamed: U46.1 (IF1), U67.2, U67.3
unnamed: U46.6 (IF2), U67.1
unnamed: U46.5 (LO1), U68.2, U68.3
unnamed: U46.4 (LO2), U68.1
unnamed: U46.2 (RF1), U69.2, U69.3
unnamed: U46.3 (RF2), U69.1
unnamed: U59.2, U59.3, U60.2, U60.3, U61.2, U61.3, U62.2, U62.3, U63.2, U63.3, U64.2, U64.3, U65.2, U65.3, U66.2, U66.3
unnamed: U72.1, U76.5
unnamed: U73.1 (IF1), U76.3 (S)
unnamed: U73.6 (IF2), U76.1 (S)
unnamed: L1.1, U73.5 (LO1), U75.3 (S)
unnamed: L2.1, U73.4 (LO2), U75.1 (S)
unnamed: U71.1 (S), U73.2 (RF1)
unnamed: U71.3 (S), U73.3 (RF2)
unnamed: U74.1, U75.5
unnamed: U80.1 (IF1), X2.1 (PRIMARY)
unnamed: U80.6 (IF2), X2.3 (PRIMARYDOT)
unnamed: U80.5 (LO1), X3.1 (PRIMARY)
unnamed: U80.4 (LO2), X3.3 (PRIMARYDOT)
unnamed: U80.2 (RF1), X1.6 (SECONDARY)
unnamed: U80.3 (RF2), X1.4 (SECONDARYDOT)
unnamed: U119.1, U119.2, U119.3
unnamed: U120.1, U120.2, U120.3
unnamed: U121.1, U121.2, U121.3
unnamed: U122.1, U122.2, U122.3
unnamed: U77.2, U77.3, X1.1 (PRIMARY)
unnamed: U77.1, X1.3 (PRIMARYDOT)
unnamed: U81.2, U81.3, X2.6 (SECONDARY)
unnamed: U81.1, X2.4 (SECONDARYDOT)
unnamed: U83.2, U83.3, X3.6 (SECONDARY)
unnamed: U83.1, X3.4 (SECONDARYDOT)

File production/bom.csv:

Designator,Footprint,Quantity,Value,LCSC Part #
"C1, C2",0805,2,10uF,C1713
"C10, C10(P49)1, C11, C12(P33)1, C13(P23)1, C15(P50)1, C3, C4, C5, C6(P10)1, C7(P1)1, C8, C8(P22)1, C9, C9(P42)1",0402,15,100nF,C1525
"C10_TD1, C10_TDV1, C11_TD1, C11_TDV1",0402,4,470pF,C701296
"C11(P43n44)1, C12_TD1, C12_TDV1, C14(P45)1, C17, C18, C25, C26, C7_TD1, C7_TDV1, C8_TD1, C8_TDV1, C9_TD1, C9_TDV1",0402,14,1uF,C14445
C12,0603,1,3pF,C46219
"C13, C14, C21, C22",0402,4,1pF,C1550
"C15, C16, C23, C24",0402,4,1nF,C106205
"C19, C20, C27, C28",0402,4,10uF,C315248
"C1_1_10_5B1, C1_1_10_5B2, C5_1_10_5B1, C5_1_10_5B2",0603,4,218.6pF,C106210
"C1_TD1, C1_TDV1, C2_TD1, C2_TDV1, C3_TD1, C3_TDV1, C4_TD1, C4_TDV1",0402,8,220nF,C295939
"C2_1_10_5B1, C2_1_10_5B2, C4_1_10_5B1, C4_1_10_5B2",0603,4,1.771nF,C318642
"C3_1_10_5B1, C3_1_10_5B2",0603,2,707.4pF,C327426
"C6, C7",0402,2,35pF,C415391
"FB1, FB10, FB12, FB13, FB14, FB15, FB2, FB3, FB4, FB5, FB6, FB7, FB8, FB9",0805,14,FerriteBead,C85840
"H1, H2, H3, H4",MountingHole_2.5mm_Pad,4,MountingHole_Pad,
J1,PinHeader_1x03_P2.54mm_Vertical,1,Conn_01x03_Pin,C429954
"J10, J11, J15, J16",PinHeader_1x02_P2.54mm_Vertical,4,Conn_01x02_Pin,C358684
"J12, J13",AUDIO-SMD_PJ-320B,2,PJ-320B,C18594
J14,PinHeader_2x07_P2.54mm_Vertical,1,Conn_02x07_Odd_Even,C71397
J17,PinHeader_2x05_P2.54mm_Vertical,1,Conn_02x05_Odd_Even,C492422
"J18, J2",PinHeader_1x04_P2.54mm_Vertical,2,Conn_01x04_Pin,C2691448
"J1_3S1, J1_3S2, J1_3S3, J1_3S4",PinHeader_1x03_P2.54mm_Vertical,4,Conn_01x03_Pin,C2937625
"J3, J4, J5",PinHeader_1x05_P2.54mm_Vertical,3,Conn_01x05_Pin,C6332198
"J6, J7, J8, J9",PinHeader_2x04_P2.54mm_Vertical,4,Conn_02x04_Counter_Clockwise,C358693
"L1, L2",0603,2,4.7nH,C1030
"L10, L13, L14, L9",L_Ferrocore_DLG-0403,4,1mH,C492286
"L11, L12, L7, L8",0603,4,1uH,C2839970
"L1_1_10_5B1, L1_1_10_5B2, L5_1_10_5B1, L5_1_10_5B2",0603,4,11.59uH,C275362
"L2_1_10_5B1, L2_1_10_5B2, L4_1_10_5B1, L4_1_10_5B2",0603,4,1.431uH,C87514
"L3, L4, L5, L6",0603,4,1nH,C41902
"L3_1_10_5B1, L3_1_10_5B2",0603,2,3.581uH,C393983
R1,0402,1,1M,C2906900
"R10, R11, R12, R9",DFN-6_L1.1-W0.7-P0.40-BL,4,FM8625H,C2857391
"R13, R14",0402,2,41.2,C270602
R15,0402,1,10,C25077
R16,0402,1,48.7,C270597
R17,0402,1,1,C25086
R18,0402,1,48.7,C270602
"R19, R21",0402,2,43,C11563
"R1_SI5351AB1, R1_TD1, R1_TDV1, R2_SI5351AB1, R2_TD1, R2_TDV1, R3_TD1, R4, R4_TD1, R7",0402,10,10K,C60490
"R2, R3",0402,2,27,C25100
"R20, R23",RES-ADJ-SMD_3313J-1,2,50,C124624
"R22, R24",0402,2,200,C25087
"R25, R29",0402,2,62,C274896
"R26, R30",0402,2,51,C25125
R27,0402,1,249,C208840
R28,0402,1,2.49k,C25884
"R31, R32",0805,2,51Ω,C17738
"R3_TDV1, R4_TDV1",RES-ADJ-SMD_3313J-1,2,2M,C124623
"R5, R6",0402,2,1K,C140196
R8,0402,1,4.7k,C25900
RP_USB1,USB_Micro-B_XKB_U254-051T-4BH83-F1S,1,USB_B_Micro,C319160
U1,QFN-56-1EP_7x7mm_P0.4mm_EP3.2x3.2mm,1,RP2040,C2040
"U10, U100, U101, U102, U103, U104, U105, U106, U107, U108, U109, U11, U110, U111, U112, U113, U114, U115, U116, U117, U118, U119, U12, U120, U121, U122, U123, U124, U125, U126, U127, U128, U129, U13, U130, U131, U132, U14, U15, U16, U17, U18, U19, U1_JU1, U1_JU2, U1_JU3, U1_JU4, U2, U20, U21, U22, U23, U24, U25, U26, U27, U28, U29, U2_JU1, U2_JU2, U2_JU3, U2_JU4, U30, U31, U32, U33, U34, U35, U36, U37, U38, U39, U3_JU1, U3_JU2, U3_JU3, U3_JU4, U40, U41, U42, U43, U44, U45, U47, U48, U49, U4_JU1, U4_JU2, U4_JU3, U4_JU4, U50, U51, U52, U53, U54, U55, U56, U57, U58, U59, U60, U61, U62, U63, U64, U65, U66, U67, U68, U69, U7, U70, U72, U74, U77, U78, U79, U8, U81, U82, U83, U84, U85, U86, U87, U88, U89, U9, U90, U91, U92, U93, U94, U95, U96, U97, U98, U99",IPEX-SMD_BWIPX-1-001E,137,BWU.FL-IPEX1,C5137195
U1_FN1,TSSOP-16_L5.0-W4.4-P0.65-LS6.4-BL,1,74HC4051,
U1_SI5351AB1,MSOP-10_3x3mm_P0.5mm,1,Si5351A-B-GT,C504891
"U1_TD1, U1_TDV1",TSSOP-16_4.4x5mm_P0.65mm,2,SN74CBT3253,C2674672
"U2_TD1, U2_TDV1",SOIC-8_3.9x4.9mm_P1.27mm,2,LM4562,C57367
U3,SOT-666,1,USBLC6-2P6,C2827693
U4,SOIC-8_5.23x5.23mm_P1.27mm,1,W25Q128JVS,C97521
"U46, U73, U80",DFN-6_L3.0-W3.0-P0.95-BL-EP-PE4140B-Z,3,PE4140B-Z,C5336176
U5,SOT-23-5,1,AP2112K-3.3,C51118
U6,QFN12_2X2X0.55_PSM,1,PE64102B-Z,
"U71, U75, U76",FILTER-SMD_ETC4-1-2TR,3,ETC1.6-4-2-3TR,C3304930
"X1, X2, X3",XFMR-SMD_6P-L7.9-W5.6-P2.54-LS7.0-BL,3,ADT1-1+,C2683432
X1_SI5351AB1,OSC-SMD_4P-L3.2-W2.5-BL,1,27MHz,C479208
Y1,Crystal_SMD_3225-4Pin_3.2x2.5mm,1,12MHz,C9002

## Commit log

2024-04-14 Working on things. Unfortunately I have to rename some components, bleh
2024-04-16 Added some switches and emi filters
2024-04-19 Added some stuff probably. Straightened out the identifiers...at least as visible in KiCAD.
2024-04-19 Dang it, IDs messed up again. Deleted second set, trying again.
2024-04-19 Cleanup
2024-04-19 Annotated schematic....
2024-04-19 Updated pcb....
2024-04-19 Tidied.... Not sure if that was a good idea or bad.
2024-04-19 Copied filter in schematic, copied filter in pcb, renamed filter components in pcb, updated pcb, saved both sides.
2024-04-19 Working on planes, started a junction. Think I want to rename them, sigh.
2024-04-19 Ok, moved it into a separate sheet....
2024-04-19 Tidied....
2024-04-19 Renamed parts on both sides....
2024-04-19 DANG IT, the filters are borked again; what gives, kicad?? I'mma go try upgrading....
2024-04-19 Updated kicad to v8
2024-04-19 Ok, now I guess we'll see if the id changes stick. ...Ok, they seem to be sticking. Maybe they've fixed the problem that necessitated "tidying" in the first place, that'd be nice.
2024-04-19 Ok, things seem to be stable, still. Sweet. Added some attenuators.
2024-04-20 Ok, I've laid out all the nets I'd completed
2024-04-21 Added some mixers, maybe
2024-04-27 Added a test mixer, laid everything out
2024-04-28 Working on a Tayloe Detector. The routing's a bit squirrely.
2024-04-28 Still working on the routing
2024-04-29 Ok, got the Tayloe Detector routed
2024-04-30 BROKEN Adding variable gain TD
2024-05-05 Fixed layout of Tayloe Detector Var. Checked DRC. Added some inductors and caps.
2024-05-06 Laid out caps and inductors. Grouped each module.
2024-05-06 Oops, missed a label
2024-05-06 Added some shorts and 50ohm loads
2024-05-07 Added a bunch of pins to the RP2040. Added a readme.
2024-05-08 Added some amps and a clock. Also tweaked tayloe pots.
2024-05-08 Added some photodiodes
2024-05-08 Whoops
2024-05-09 Added dc boost, constant current driver, and some LEDs.
2024-05-09 Added some transistors.
2024-05-09 Added (bad) differential de/mux
2024-05-09 Added some filters. Decided to remove the unfinished 'programmable filter net', for several reasons.
2024-05-09 Packed the board
2024-05-09 Added a speaker!
2024-05-09 Added some mics
2024-05-09 Added some buttons and an LED (just to fill space, for monkey brain)
2024-05-09 Added blackberry cane graphic (it's kinda big, bogs down rendering)
2024-05-09 Added list of stuff to README
